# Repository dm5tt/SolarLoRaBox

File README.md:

# What is this thing?

This is an experimental platform for an solar driven LoRa sensor station based on the

- Microcontroller: ST STM32U083CCT6
- Radio: Heltec HT-RA62 (Semtech SX1262)
- Charging Controller: TI BQ25185
- Flash: Windbond W25Q128JVS (128 MBit)
- Reset IC: APX803L05-32SA-7 (3.2V)
- LDO: HEERMICR HE9073A30MR (3.0V)

Plan is to´ use it as platform for a wireless sensor based on Zephyr.

# Features

 - Solar Input up to 18V (24V survival)
 - 3A maximum load
 - 1A maximum charge current
 - Pseudo-MPPT (VINDPM)
 - Power Path (= if the battery is fully charged and there's enough solar power the device is getting powered directly from solar. It also can mix battery and solar energy.)
 - Two ADC signals for getting VLOAD and  VBUS voltage using voltage dividers
 - 3.7V LiPo either via 18650 block or JST-PH 2.0 connector

Lots if this stuff was already proven and validated in the project [SolarMeshtasticNode](https://github.com/dm5tt/SolarMeshtasticNode).

# Interfaces

- 4x I2C

- 1x UART

- 1x USB

- 1x GPIO with 4 available pins

# Programming interfaces

The STM32U0 spits out its bootloader on the I2C, UART and USB.

For "comfort programming" it has a TC2030 where you can connect a Segger or ST-Link

# Firmware

LoRa with Zephyr and TheThingsNetwork is already running :-)

Firmware integration tests are [here](https://github.com/dm5tt/SolarLoRaBox_Firmware)

# Evaluation

[Verification of PCB v0.0.1](EVALUATION-v001.md)

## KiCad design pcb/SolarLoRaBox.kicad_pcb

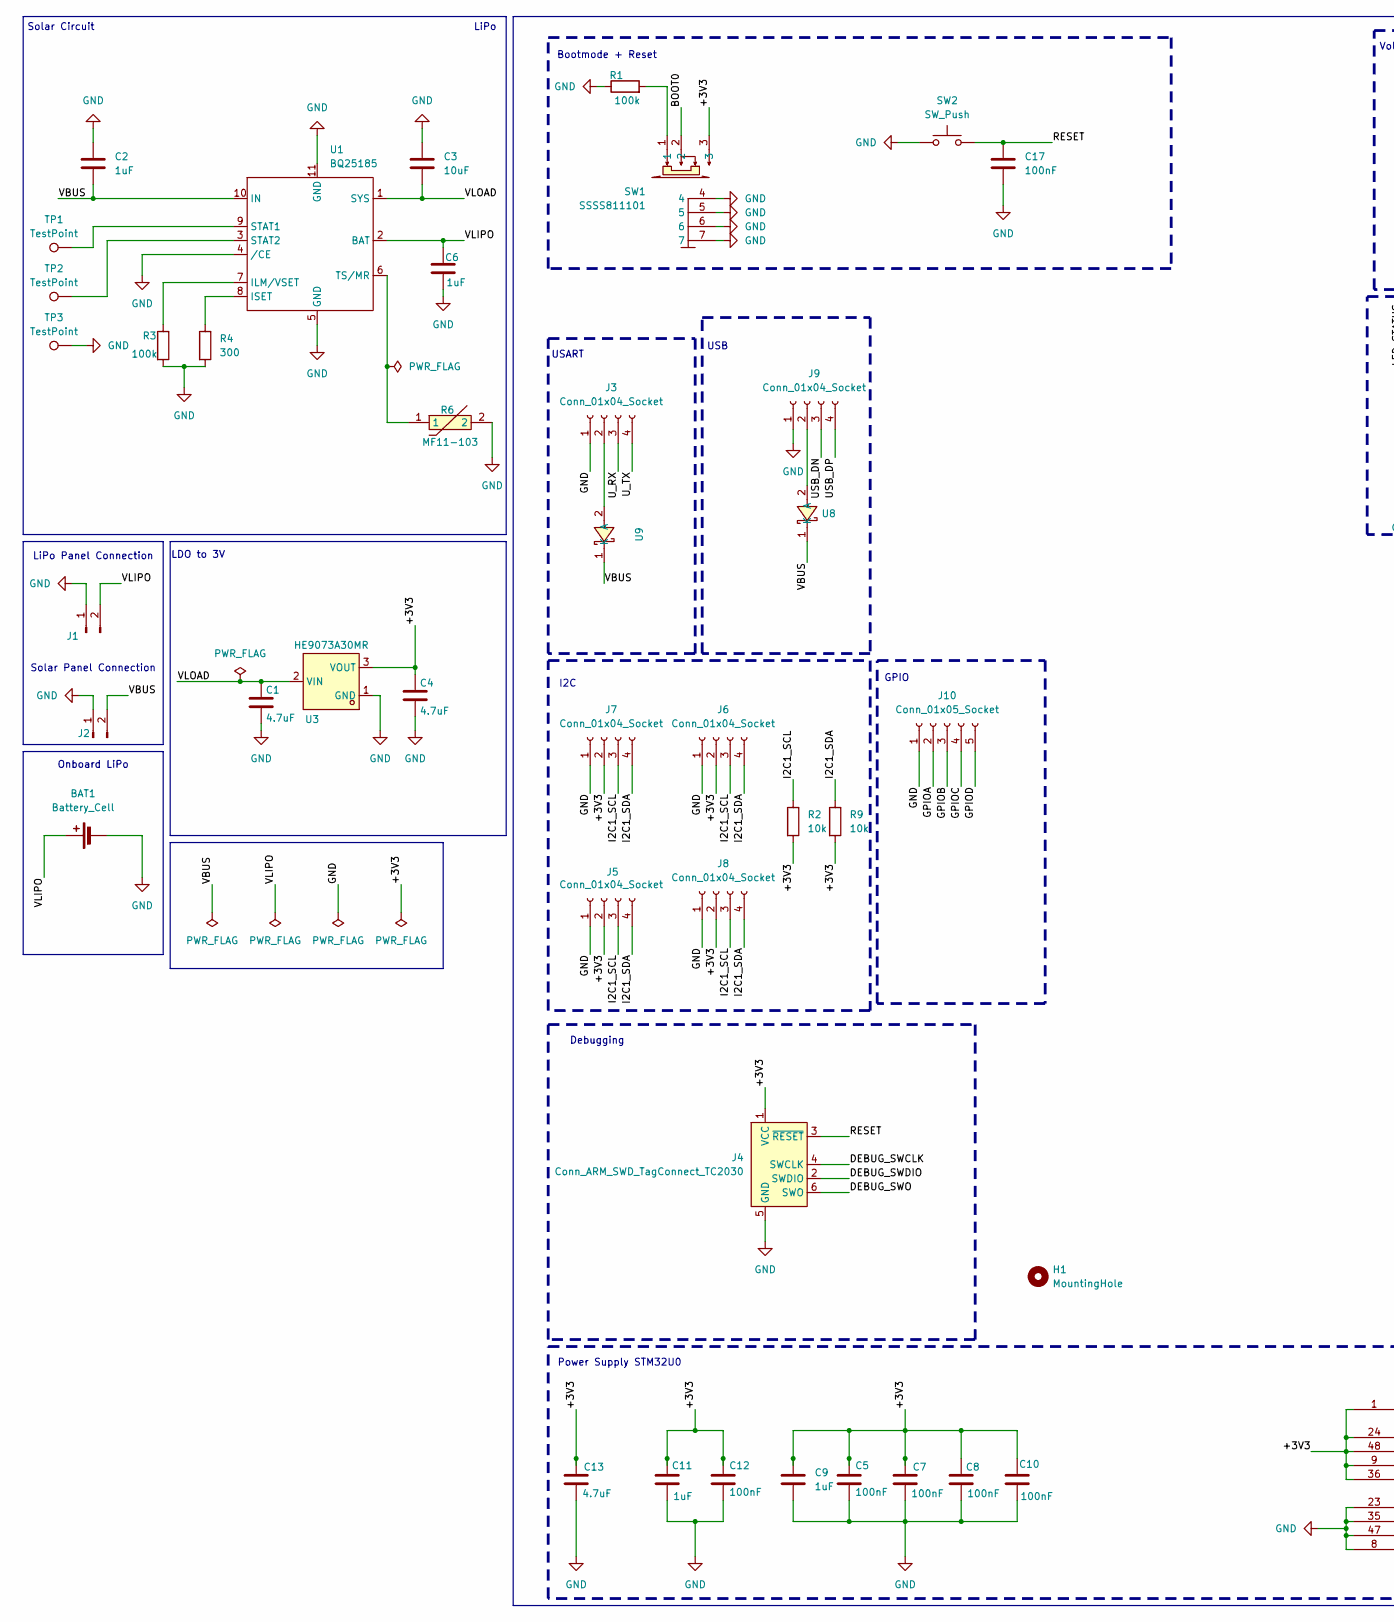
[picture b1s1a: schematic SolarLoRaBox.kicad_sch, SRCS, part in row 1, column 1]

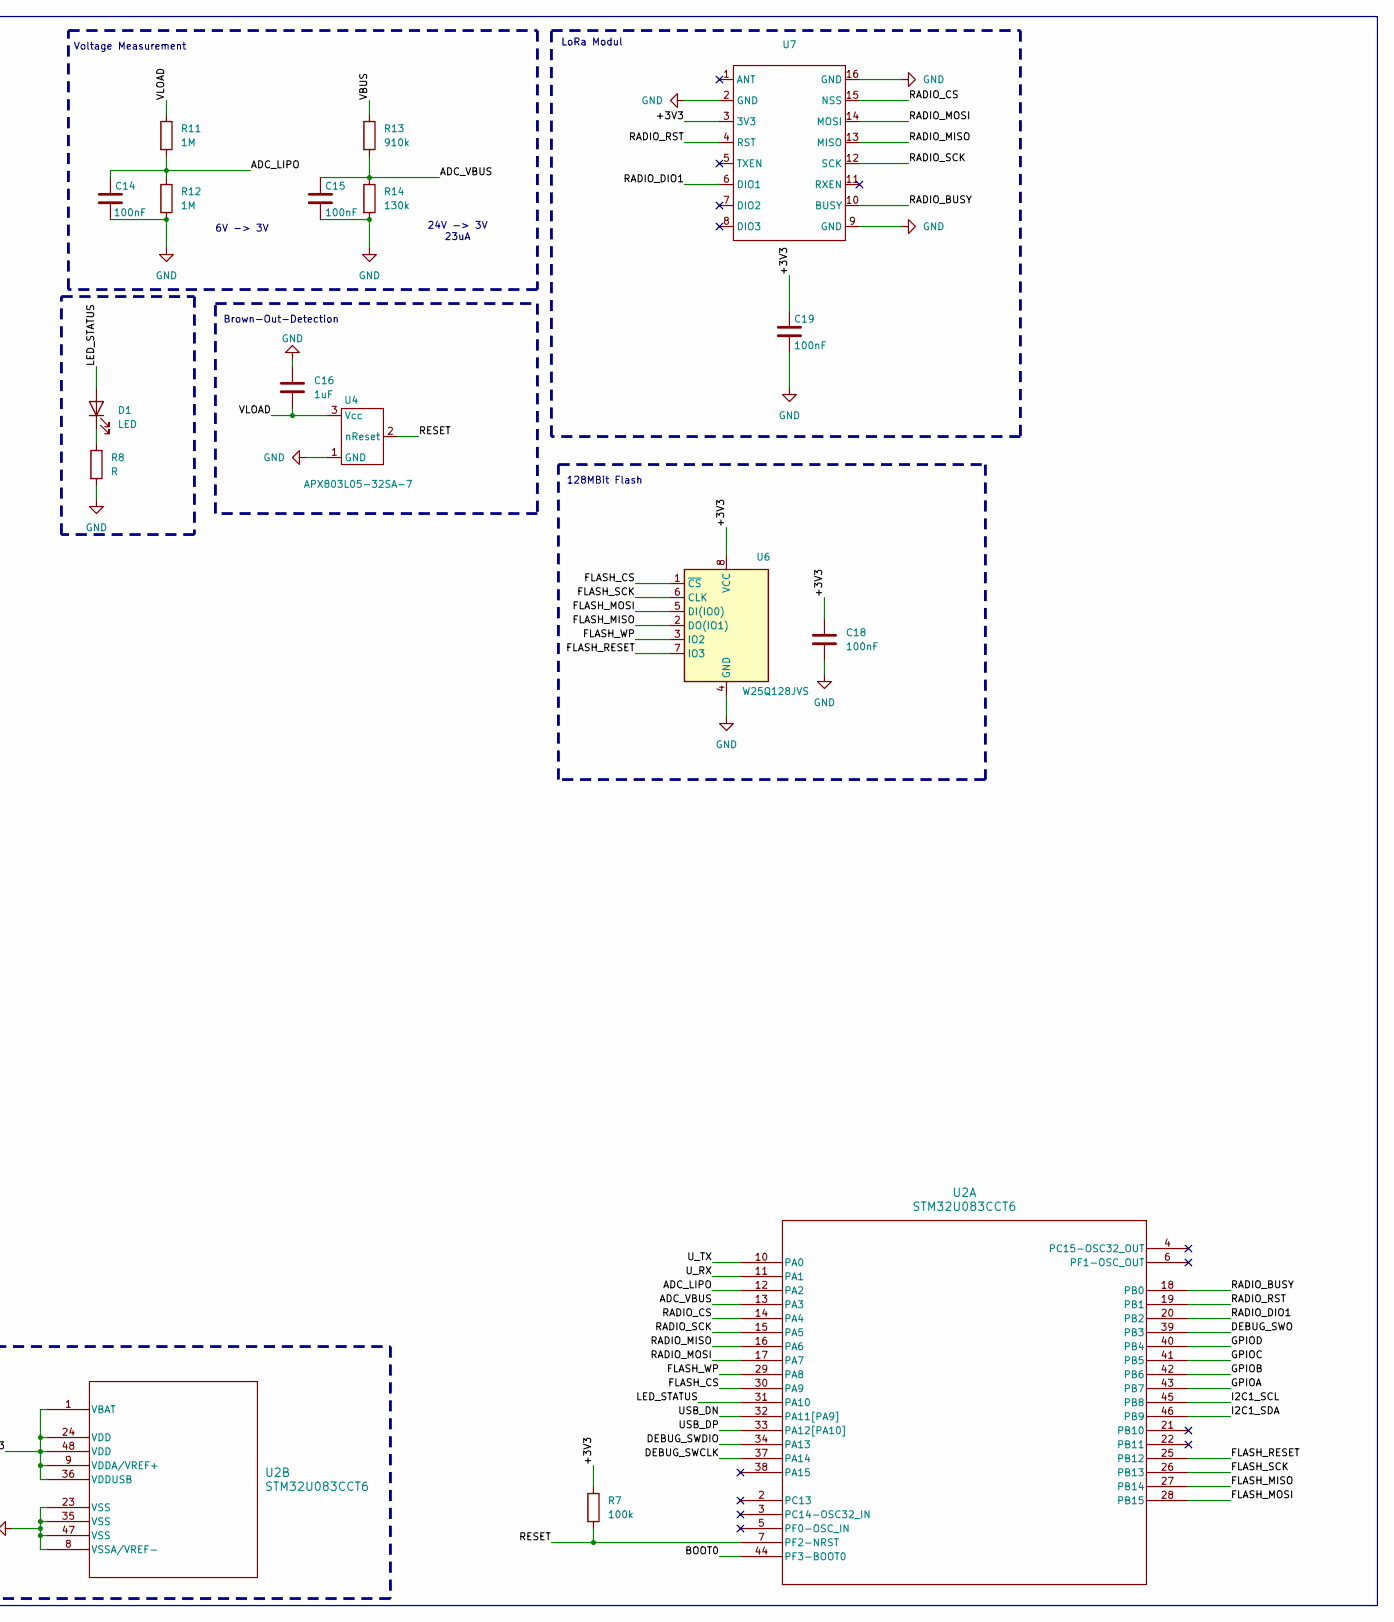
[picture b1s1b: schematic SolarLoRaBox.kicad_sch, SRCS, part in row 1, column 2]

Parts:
BAT1: Battery_Cell; BAT-TH_BH-18650-A1AJ005
C1, C4, C13: 4.7uF; C_0805_2012Metric_Pad1.18x1.45mm_HandSolder
C2, C6, C9, C11, C16: 1uF; C_0805_2012Metric_Pad1.18x1.45mm_HandSolder
C3: 10uF; C_0805_2012Metric_Pad1.18x1.45mm_HandSolder
C5, C7, C8, C10, C12, C14, C15, C17, C18, C19: 100nF; C_0805_2012Metric_Pad1.18x1.45mm_HandSolder
D1: LED; LED_0805_2012Metric
H1: MountingHole; MountingHole_4.3mm_M4_DIN965
J1, J2: Conn_01x02_Socket; JST_PH_B2B-PH-K_1x02_P2.00mm_Vertical
J3, J5, J6, J7, J8, J9: Conn_01x04_Socket; JST_PH_B4B-PH-K_1x04_P2.00mm_Vertical
J4: Conn_ARM_SWD_TagConnect_TC2030; Tag-Connect_TC2030-IDC-FP_2x03_P1.27mm_Vertical
J10: Conn_01x05_Socket; JST_PH_B5B-PH-K_1x05_P2.00mm_Vertical
R1, R3, R7: 100k; R_0805_2012Metric_Pad1.20x1.40mm_HandSolder
R2, R9: 10k; R_0805_2012Metric_Pad1.20x1.40mm_HandSolder
R4: 300; R_0805_2012Metric_Pad1.20x1.40mm_HandSolder
R6: MF11-103; RES-TH_L6.5-W4.0-P2.50-D0.5; LCSC Part C70913
R8: R; R_0805_2012Metric_Pad1.20x1.40mm_HandSolder
R11, R12: 1M; R_0805_2012Metric_Pad1.20x1.40mm_HandSolder
R13: 910k; R_0805_2012Metric_Pad1.20x1.40mm_HandSolder
R14: 130k; R_0805_2012Metric_Pad1.20x1.40mm_HandSolder
SW1: SSSS811101; SW-SMD_SSSS811101; LCSC Part C109335
SW2: SW_Push; SW_PUSH_6mm
TP1, TP2, TP3: TestPoint; TestPoint_Pad_2.0x2.0mm
U1: BQ25185; SON40P220X200X80-11N
U2: STM32U083CCT6; LQFP48_STM
U3: HE9073A30MR; SOT-23-3_L2.9-W1.6-P1.90-LS2.8-BR-CW; LCSC Part C723793
U4: APX803L05-32SA-7; SOT23-3
U6: W25Q128JVS; SOIC-8_5.23x5.23mm_P1.27mm
U7: HT-RA62
U8, U9: SS26_C5350986; SMA_L4.3-W2.6-LS5.1-RD; LCSC Part C5350986

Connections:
/+3V3: C4.1, C5.1, C7.1, C8.1, C9.1, C10.1, C11.1, C12.1, C13.1, C18.1, C19.1, J4.1 (VCC), J5.2, J6.2, J7.2, J8.2, R2.2, R7.1, R9.2, SW1.3, U2.1 (VBAT), U2.9 (VDDA/VREF+), U2.24 (VDD), U2.36 (VDDUSB), U2.48 (VDD), U3.3 (VOUT), U6.8 (VCC), U7.3 (3V3)
/ADC_LIPO: C14.1, R11.2, R12.1, U2.12 (PA2)
/ADC_VBUS: C15.1, R13.2, R14.1, U2.13 (PA3)
/BOOT0: SW1.2, U2.44 (PF3-BOOT0)
/DEBUG_SWCLK: J4.4 (SWCLK), U2.37 (PA14)
/DEBUG_SWDIO: J4.2 (SWDIO), U2.34 (PA13)
/DEBUG_SWO: J4.6 (SWO), U2.39 (PB3)
/FLASH_CS: U2.30 (PA9), U6.1 (~CS)
/FLASH_MISO: U2.27 (PB14), U6.2 (DO(IO1))
/FLASH_MOSI: U2.28 (PB15), U6.5 (DI(IO0))
/FLASH_RESET: U2.25 (PB12), U6.7 (IO3)
/FLASH_SCK: U2.26 (PB13), U6.6 (CLK)
/FLASH_WP: U2.29 (PA8), U6.3 (IO2)
/GPIOA: J10.2, U2.43 (PB7)
/GPIOB: J10.3, U2.42 (PB6)
/GPIOC: J10.4, U2.41 (PB5)
/GPIOD: J10.5, U2.40 (PB4)
/I2C1_SCL: J5.3, J6.3, J7.3, J8.3, R2.1, U2.45 (PB8)
/I2C1_SDA: J5.4, J6.4, J7.4, J8.4, R9.1, U2.46 (PB9)
/LED_STATUS: D1.2 (A), U2.31 (PA10)
/RADIO_BUSY: U2.18 (PB0), U7.10 (BUSY)
/RADIO_CS: U2.14 (PA4), U7.15 (NSS)
/RADIO_DIO1: U2.20 (PB2), U7.6 (DIO1)
/RADIO_MISO: U2.16 (PA6), U7.13 (MISO)
/RADIO_MOSI: U2.17 (PA7), U7.14 (MOSI)
/RADIO_RST: U2.19 (PB1), U7.4 (RST)
/RADIO_SCK: U2.15 (PA5), U7.12 (SCK)
/RESET: C17.1, J4.3 (~RESET), R7.2, SW2.2, U2.7 (PF2-NRST), U4.2 (nReset)
/USB_DN: J9.3, U2.32 (PA11[PA9])
/USB_DP: J9.4, U2.33 (PA12[PA10])
/U_RX: J3.3, U2.11 (PA1)
/U_TX: J3.4, U2.10 (PA0)
/VBUS: C2.2, J2.2, R13.1, U1.10 (IN), U8.1 (K), U9.1 (K)
/VLIPO: BAT1.1 (+), C6.1, J1.2, U1.2 (BAT)
/VLOAD: C1.1, C3.2, C16.2, R11.1, U1.1 (SYS), U3.2 (VIN), U4.3 (Vcc)
GND: BAT1.2 (-), C1.2, C2.1, C3.1, C4.2, C5.2, C6.2, C7.2, C8.2, C9.2, C10.2, C11.2, C12.2, C13.2, C14.2, C15.2, C16.1, C17.2, C18.2, C19.2, J1.1, J2.1, J3.1, J4.5 (GND), J5.1, J6.1, J7.1, J8.1, J9.1, J10.1, R1.1, R3.2, R4.2, R6.2, R8.2, R12.2, R14.2, SW1.4, SW1.5, SW1.6, SW1.7, SW2.1, TP3.1, U1.4 (/CE), U1.5 (GND), U1.11 (GND), U2.8 (VSSA/VREF-), U2.23 (VSS), U2.35 (VSS), U2.47 (VSS), U3.1 (GND), U4.1 (GND), U6.4 (GND), U7.2 (GND), U7.9 (GND), U7.16 (GND)
unnamed: D1.1 (K), R8.1
unnamed: J3.2, U9.2 (A)
unnamed: J9.2, U8.2 (A)
unnamed: R1.2, SW1.1
unnamed: R3.1, U1.7 (ILM/VSET)
unnamed: R4.1, U1.8 (ISET)
unnamed: TP1.1, U1.9 (STAT1)
unnamed: TP2.1, U1.3 (STAT2)
unnamed: R6.1, U1.6 (TS/MR)

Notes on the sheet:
Solar Circuit
Bootmode + Reset
Power Supply STM32U0
6V -> 3V
USART
Voltage Measurement
Debugging
LiPo
LiPo Panel Connection
USB
GPIO
Brown-Out-Detection
Onboard LiPo
Solar Panel Connection
LDO to 3V
I2C
128MBit Flash
LoRa Modul
24V -> 3V 23uA

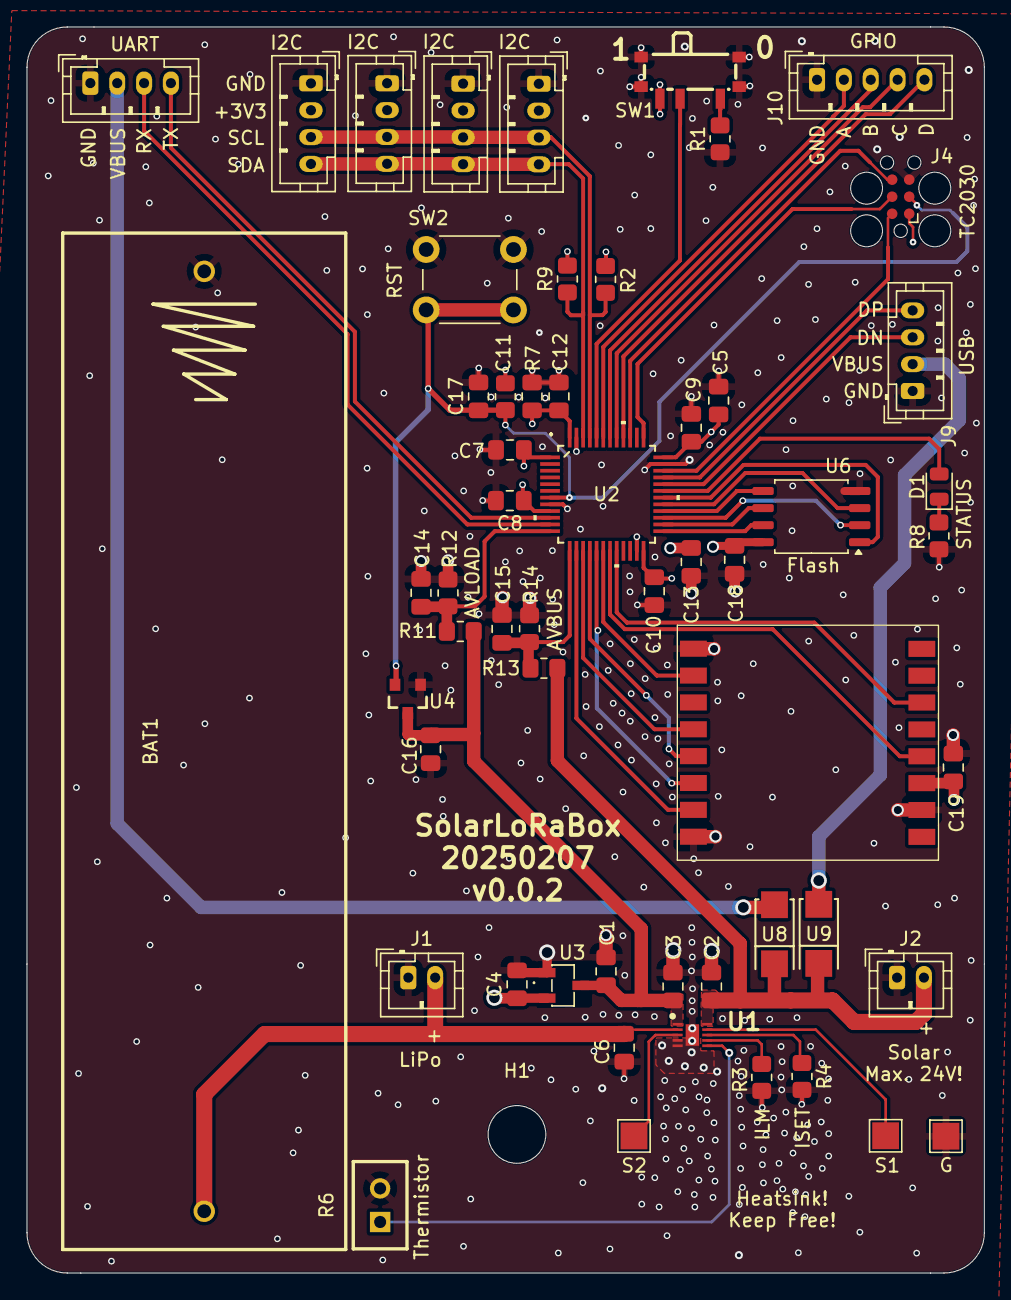
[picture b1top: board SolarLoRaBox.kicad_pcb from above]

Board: 4 copper layers, 71.3 x 92.8 mm, 57 parts (0 on the bottom side), 45 nets.

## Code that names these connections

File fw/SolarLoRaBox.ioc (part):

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Mcu.Name=STM32U083CCTx
Mcu.Package=LQFP48
Mcu.UserName=STM32U083CCTx
PA0.Mode=Asynchronous
PA0.Signal=USART4_TX
PA1.Mode=Asynchronous
PA1.Signal=USART4_RX
PA11\ [PA9].Mode=Device
PA11\ [PA9].Signal=USB_DM
PA12\ [PA10].Mode=Device
PA12\ [PA10].Signal=USB_DP
PA13\ (SWDIO).Mode=Trace_Asynchronous_SW
PA13\ (SWDIO).Signal=DEBUG_JTMS-SWDIO
PA14\ (SWCLK).Mode=Trace_Asynchronous_SW
PA14\ (SWCLK).Signal=DEBUG_JTCK-SWCLK
PA2.GPIOParameters=GPIO_Label
PA2.GPIO_Label=ADC_LIPO
PA2.Mode=IN6
PA2.Signal=ADC1_IN6
PA3.GPIOParameters=GPIO_Label
PA3.GPIO_Label=ADC_VBUS
PA3.Mode=IN7
PA3.Signal=ADC1_IN7
PA4.GPIOParameters=GPIO_Label
PA4.GPIO_Label=RADIO_CS
PA4.Signal=GPIO_Output
PA5.GPIOParameters=GPIO_Label
PA5.GPIO_Label=RADIO_SCK
PA5.Mode=Full_Duplex_Master
PA5.Signal=SPI1_SCK
PA6.GPIOParameters=GPIO_Label
PA6.GPIO_Label=RADIO_MISO
PA6.Mode=Full_Duplex_Master
PA6.Signal=SPI1_MISO
PA7.GPIOParameters=GPIO_Label
PA7.GPIO_Label=RADIO_MOSI
PA7.Mode=Full_Duplex_Master
PA7.Signal=SPI1_MOSI
PA8.GPIOParameters=GPIO_Label
PA8.GPIO_Label=FLASH_WP
PA8.Signal=GPIO_Output
PA9.GPIOParameters=GPIO_Label
PA9.GPIO_Label=FLASH_RESET
PA9.Signal=GPIO_Output
PB0.GPIOParameters=GPIO_Label
PB0.GPIO_Label=RADIO_BUSY
PB0.Signal=GPIO_Input
PB1.GPIOParameters=GPIO_Label
PB1.GPIO_Label=RADIOR_RST
PB1.Signal=GPIO_Output
PB12.GPIOParameters=GPIO_Label
PB12.GPIO_Label=FLASH_CS
PB12.Signal=GPIO_Output
PB13.GPIOParameters=GPIO_Label
PB13.GPIO_Label=FLASH_SCK
PB13.Mode=Full_Duplex_Master
PB13.Signal=SPI2_SCK
PB14.GPIOParameters=GPIO_Label
PB14.GPIO_Label=FLASH_MISO
PB14.Mode=Full_Duplex_Master
PB14.Signal=SPI2_MISO
PB15.GPIOParameters=GPIO_Label
PB15.GPIO_Label=FLASH_MOSI
PB15.Mode=Full_Duplex_Master
PB15.Signal=SPI2_MOSI
PB2.GPIOParameters=GPIO_Label
PB2.GPIO_Label=RADIO_DIO1
PB2.Signal=GPIO_Input
PB3.Mode=Trace_Asynchronous_SW
PB3.Signal=DEBUG_JTDO-SWO
PB7.GPIOParameters=GPIO_Label
PB7.GPIO_Label=LED_STATUS
PB7.Signal=GPIO_Output
PB8.Mode=I2C
PB8.Signal=I2C1_SCL
PB9.Mode=I2C
PB9.Signal=I2C1_SDA
RCC.HSE_VALUE=4000000
RCC.SYSCLKFreq_VALUE=16000000
board=custom

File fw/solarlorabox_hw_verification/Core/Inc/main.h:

/* USER CODE BEGIN Header */
/**
  ******************************************************************************
  * @file           : main.h
  * @brief          : Header for main.c file.
  *                   This file contains the common defines of the application.
  ******************************************************************************
  * @attention
  *
  * Copyright (c) 2025 STMicroelectronics.
  * All rights reserved.
  *
  * This software is licensed under terms that can be found in the LICENSE file
  * in the root directory of this software component.
  * If no LICENSE file comes with this software, it is provided AS-IS.
  *
  ******************************************************************************
  */
/* USER CODE END Header */

/* Define to prevent recursive inclusion -------------------------------------*/
#ifndef __MAIN_H
#define __MAIN_H

#ifdef __cplusplus
extern "C" {
#endif

/* Includes ------------------------------------------------------------------*/
#include "stm32u0xx_hal.h"

/* Private includes ----------------------------------------------------------*/
/* USER CODE BEGIN Includes */

/* USER CODE END Includes */

/* Exported types ------------------------------------------------------------*/
/* USER CODE BEGIN ET */

/* USER CODE END ET */

/* Exported constants --------------------------------------------------------*/
/* USER CODE BEGIN EC */

/* USER CODE END EC */

/* Exported macro ------------------------------------------------------------*/
/* USER CODE BEGIN EM */

/* USER CODE END EM */

/* Exported functions prototypes ---------------------------------------------*/
void Error_Handler(void);

/* USER CODE BEGIN EFP */

/* USER CODE END EFP */

/* Private defines -----------------------------------------------------------*/
#define ADC_LIPO_Pin GPIO_PIN_2
#define ADC_LIPO_GPIO_Port GPIOA
#define ADC_VBUS_Pin GPIO_PIN_3
#define ADC_VBUS_GPIO_Port GPIOA
#define RADIO_CS_Pin GPIO_PIN_4
#define RADIO_CS_GPIO_Port GPIOA
#define RADIO_SCK_Pin GPIO_PIN_5
#define RADIO_SCK_GPIO_Port GPIOA
#define RADIO_MISO_Pin GPIO_PIN_6
#define RADIO_MISO_GPIO_Port GPIOA
#define RADIO_MOSI_Pin GPIO_PIN_7
#define RADIO_MOSI_GPIO_Port GPIOA
#define RADIO_BUSY_Pin GPIO_PIN_0
#define RADIO_BUSY_GPIO_Port GPIOB
#define RADIOR_RST_Pin GPIO_PIN_1
#define RADIOR_RST_GPIO_Port GPIOB
#define RADIO_DIO1_Pin GPIO_PIN_2
#define RADIO_DIO1_GPIO_Port GPIOB
#define FLASH_RESET_Pin GPIO_PIN_12
#define FLASH_RESET_GPIO_Port GPIOB
#define FLASH_SCK_Pin GPIO_PIN_13
#define FLASH_SCK_GPIO_Port GPIOB
#define FLASH_MISO_Pin GPIO_PIN_14
#define FLASH_MISO_GPIO_Port GPIOB
#define FLASH_MOSI_Pin GPIO_PIN_15
#define FLASH_MOSI_GPIO_Port GPIOB
#define FLASH_WP_Pin GPIO_PIN_8
#define FLASH_WP_GPIO_Port GPIOA
#define FLASH_CS_Pin GPIO_PIN_9
#define FLASH_CS_GPIO_Port GPIOA
#define LED_STATUS_Pin GPIO_PIN_10
#define LED_STATUS_GPIO_Port GPIOA

/* USER CODE BEGIN Private defines */

/* USER CODE END Private defines */

#ifdef __cplusplus
}
#endif

#endif /* __MAIN_H */

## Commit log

2025-01-16 doc: replace picture
2025-01-16 pcb: rework heatsink area below the solar charging controller
2025-01-16 README: add version to hw verification
2025-01-16 README: remove "testing of"
2025-01-17 pcb, sch: fix invalid uart rx/tx silk print, add C infront of reset ic
2025-01-17 Updates pictures and reorganize structure a bit
2025-01-17 pcb, sch, doc: lots of cosmetic fixes
2025-01-17 pcb, sch: more eyecandy
2025-01-21 EVALUATION: God damn wit
2025-01-21 EVALUATION-v001: fix broken comment
2025-01-21 EVALUATION-v001: be even more precise about the Reset IC
2025-01-21 EVALUATION-v001: Formatting
2025-01-21 EVALUATION: fix typo
2025-01-21 EVALUATION-v001: Found a beautiful UTF-8 icon to mark WIP points
2025-01-21 pcb, sch: switch MISO/MOSI on Windbond flash as they are inverted!
2025-01-21 EVALUATION-v001: move to right chapter
2025-01-21 EVALUATION-v001: add LED
2025-01-21 EVALUATION-v001: Update
2025-01-21 EVALUATION-v001: SPI for the flash
2025-01-21 EVALUATION: ADC verified
2025-01-21 pcb, sch: match silk print and schematic
2025-02-09 pcb: non functional changes
2025-03-13 README: add link to firmware
2025-03-22 EVALUATION-v001: add run test
